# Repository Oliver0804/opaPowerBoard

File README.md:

# opaPowerBoard
## VER 1.0 202306

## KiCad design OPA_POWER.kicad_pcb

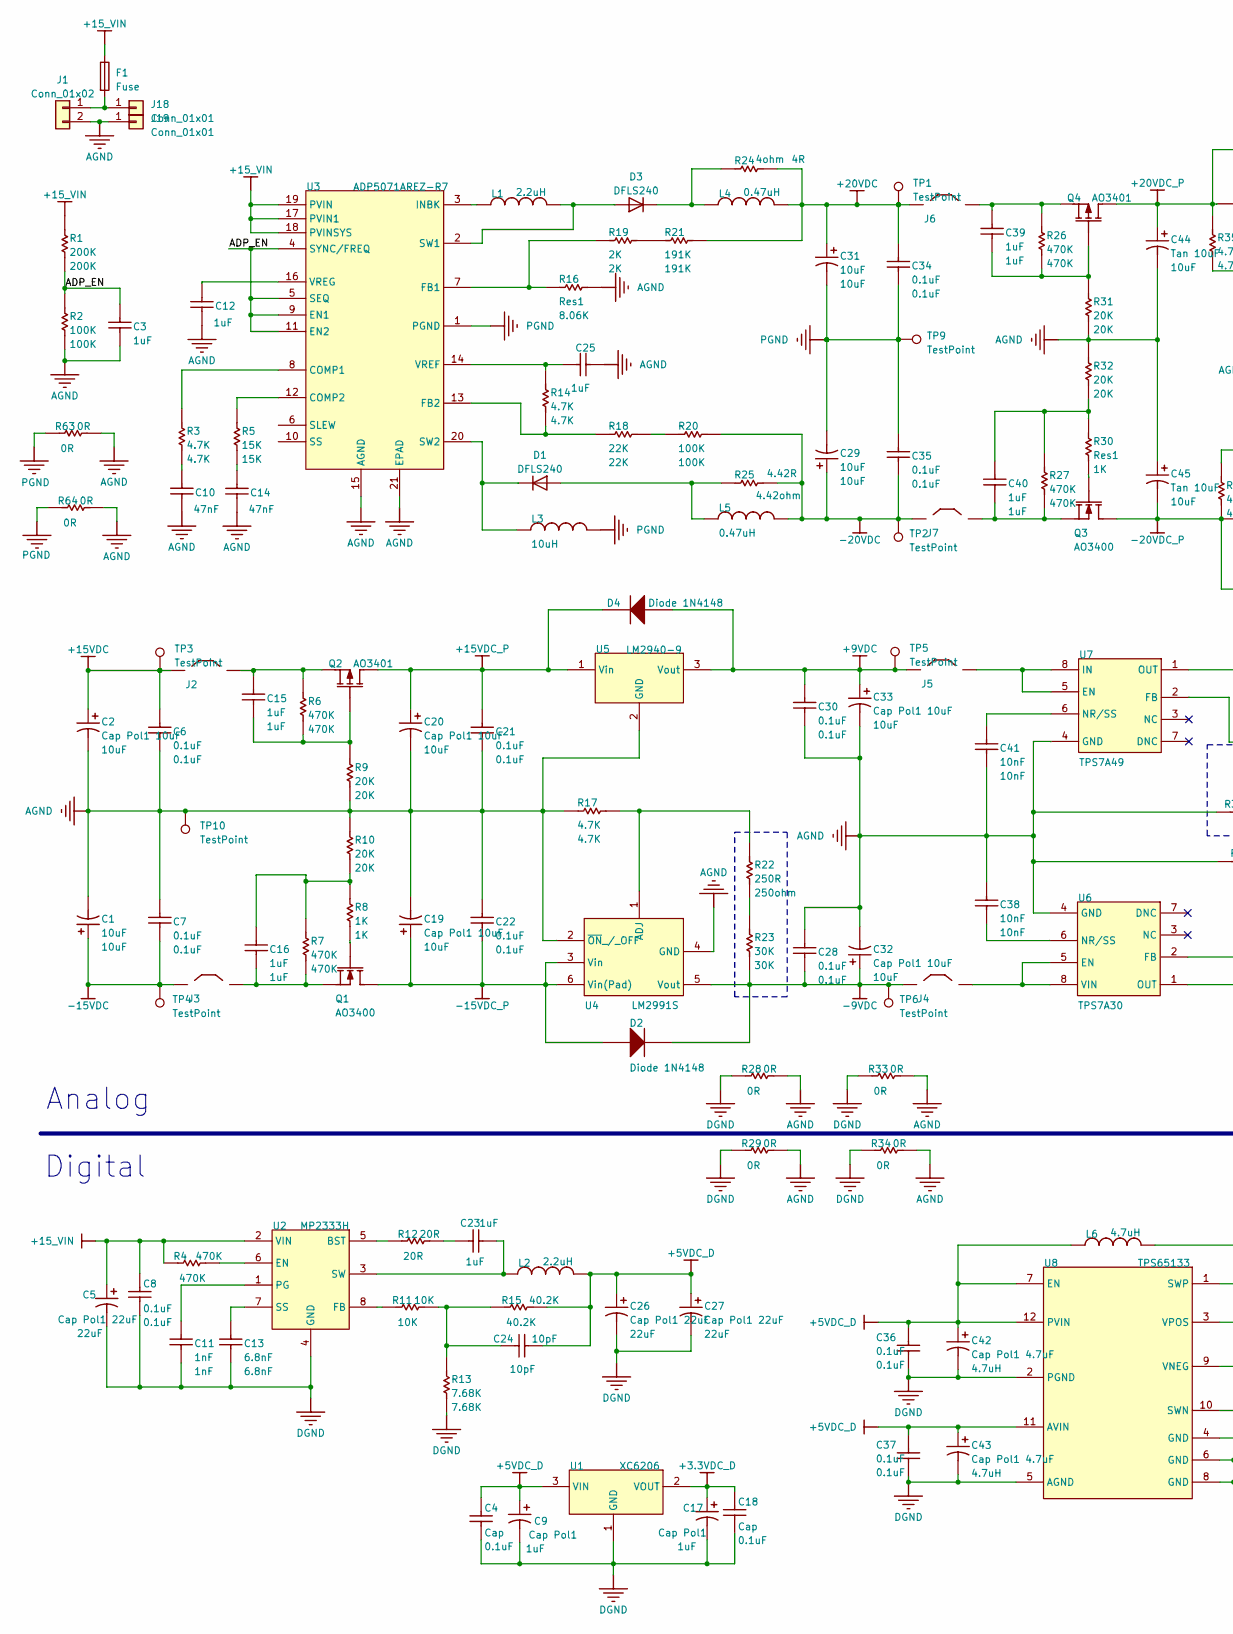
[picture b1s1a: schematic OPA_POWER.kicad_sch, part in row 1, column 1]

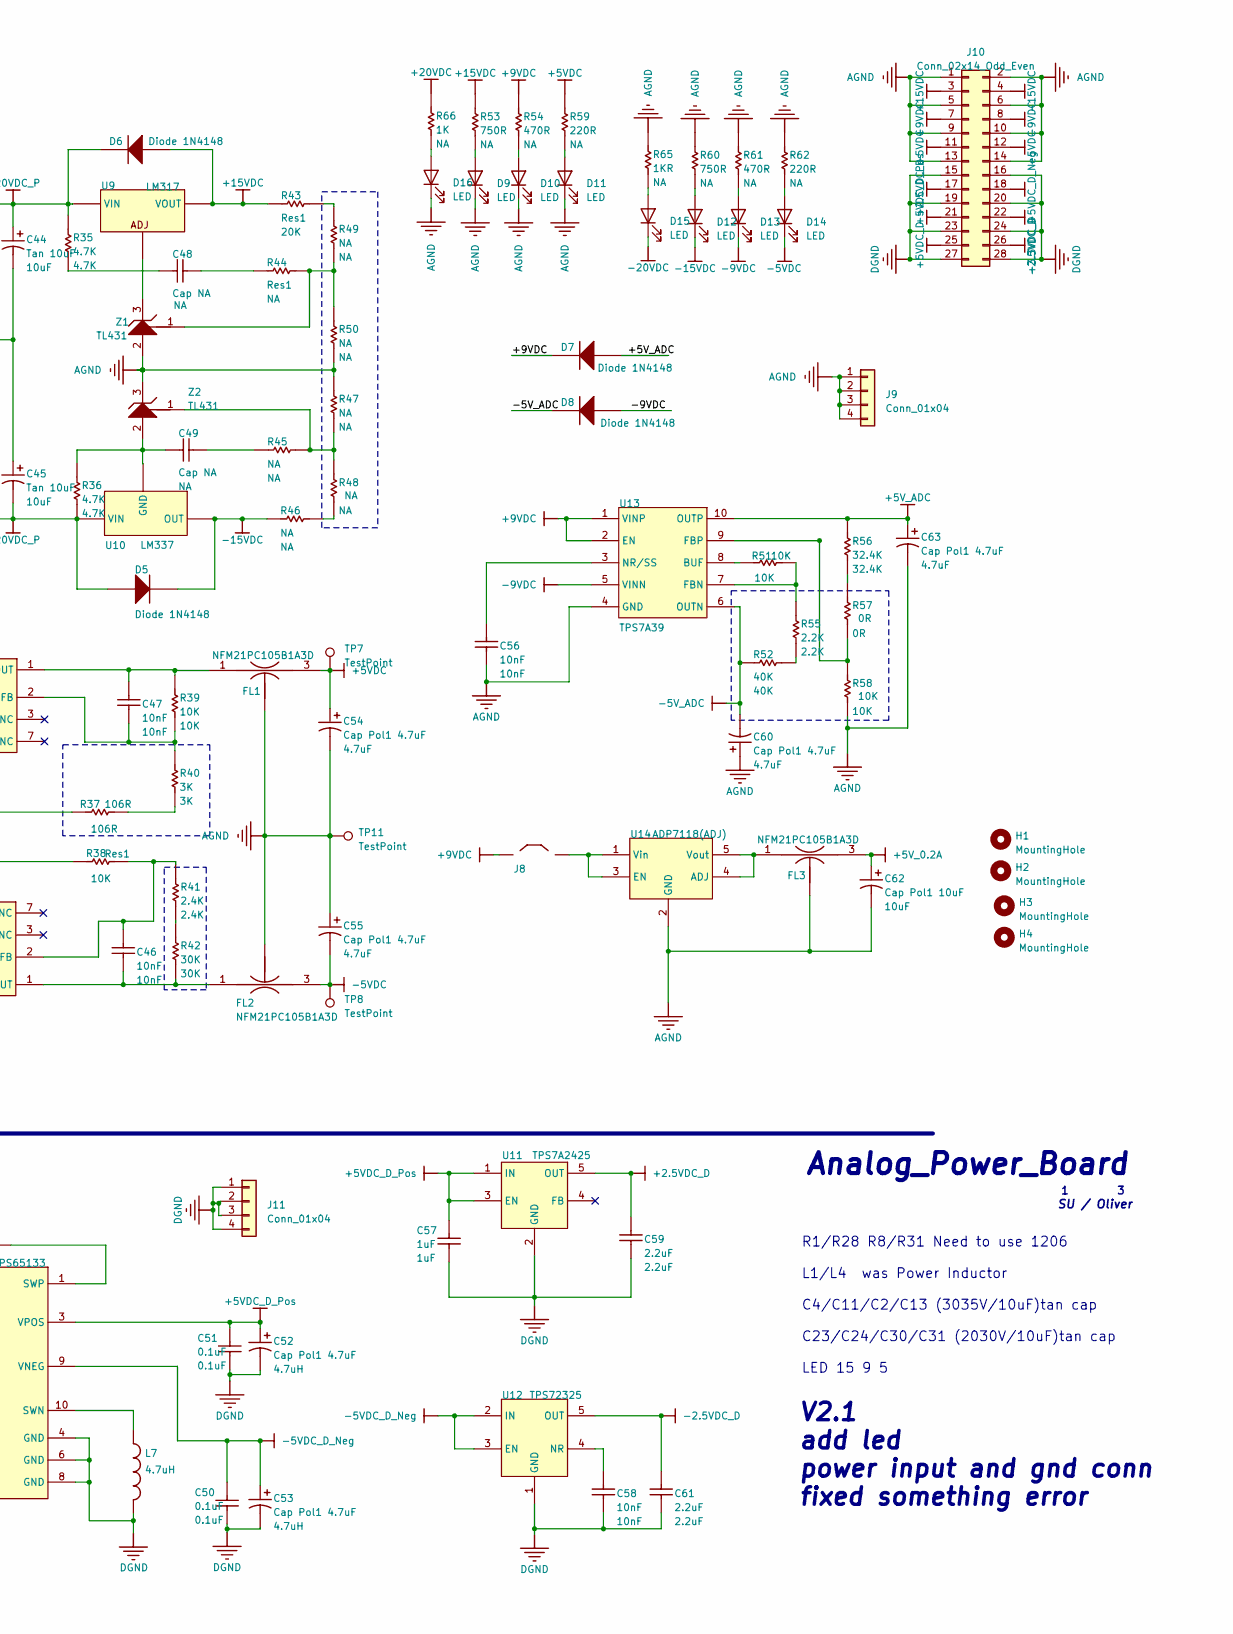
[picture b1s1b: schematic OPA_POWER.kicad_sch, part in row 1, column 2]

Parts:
C1, C29, C31: 10uF; CP_EIA-7343-20_Kemet-V
C2, C19, C20: Cap Pol1 10uF; CP_EIA-7343-20_Kemet-V
C3, C12, C15, C16, C23, C25, C39, C40, C57: 1uF; C_0603_1608Metric
C4, C18: Cap; C_0603_1608Metric
C5, C26, C27: Cap Pol1 22uF; CP_EIA-3528-12_Kemet-T
C6, C7, C8, C21, C22, C28, C30, C34, C35, C36, C37, C50, C51: 0.1uF; C_0603_1608Metric
C9, C17: Cap Pol1; CP_EIA-3528-12_Kemet-T
C10, C14: 47nF; C_0603_1608Metric
C11: 1nF; C_0603_1608Metric
C13: 6.8nF; C_0603_1608Metric
C24: 10pF; C_0603_1608Metric
C32, C33, C62: Cap Pol1 10uF; CP_EIA-3528-12_Kemet-T
C38, C41, C46, C47, C56, C58: 10nF; C_0603_1608Metric
C42, C52, C54: Cap Pol1 4.7uF; CP_EIA-3528-12_Kemet-T_Pad1.50x2.35mm_HandSolder
C43, C53, C55, C60, C63: Cap Pol1 4.7uF; CP_EIA-3528-12_Kemet-T
C44, C45: Tan 10uF; CP_EIA-7343-20_Kemet-V
C48, C49: Cap NA; C_0603_1608Metric
C59, C61: 2.2uF; C_0603_1608Metric
D1, D3: DFLS240; D_SOD-123
D2, D4, D5, D6, D7, D8: Diode 1N4148; D_SOD-323
D9, D10, D11, D12, D13, D14, D15, D16: LED; LED_0201_0603Metric
F1: Fuse; Fuse_1210_3225Metric
FL1, FL2, FL3: NFM21PC105B1A3D; FIL_NFM21PC105B1A3D
H1, H2, H3, H4: MountingHole; MountingHole_3mm_Pad_Via
J1: Conn_01x02; PinHeader_1x02_P2.54mm_Vertical
J2, J3, J4, J5, J6, J7, J8: Jumper; PinHeader_2x01_P2.54mm_Vertical
J9, J11: Conn_01x04; PinHeader_1x04_P2.54mm_Vertical
J10: Conn_02x14_Odd_Even; PinHeader_2x14_P2.54mm_Vertical
J18, J19: Conn_01x01; TestPoint_Pad_4.0x4.0mm
L1: 2.2uH; L_Vishay_IHLP-6767
L2: 2.2uH; L_Sunlord_SWPA3010S
L3: 10uH; L_Vishay_IHLP-6767
L4: 0.47uH; L_Sunlord_SWPA3010S
L5, L6: Inductor; L_Sunlord_SWPA3010S
L7: 4.7uH; L_Sunlord_SWPA3010S
Q1, Q3: AO3400; SOT-23
Q2, Q4: AO3401; SOT-23
R1: 200K; R_0603_1608Metric
R2, R20: 100K; R_0603_1608Metric
R3, R14, R17: 4.7K; R_0603_1608Metric
R4, R6, R7, R26, R27: 470K; R_0603_1608Metric
R5: 15K; R_0603_1608Metric
R8, R66: 1K; R_0603_1608Metric
R9, R10, R31, R32: 20K; R_0603_1608Metric
R11, R39, R51, R58: 10K; R_0603_1608Metric
R12: 20R; R_0603_1608Metric
R13: 7.68K; R_0603_1608Metric
R15: 40.2K; R_0603_1608Metric
R16, R30, R38, R43, R44: Res1; R_0603_1608Metric
R18: 22K; R_0603_1608Metric
R19: 2K; R_0603_1608Metric
R21: 191K; R_0603_1608Metric
R22: 250R; R_0603_1608Metric
R23, R42: 30K; R_0603_1608Metric
R24: 4R; R_1206_3216Metric
R25: 4.42R; R_1206_3216Metric
R28, R29, R33, R34, R57, R63, R64: 0R; R_0603_1608Metric
R35, R36: 4.7K; R_1206_3216Metric
R37: 106R; R_0603_1608Metric
R40: 3K; R_0603_1608Metric
R41: 2.4K; R_0603_1608Metric
R45, R46, R47, R48, R49, R50: NA; R_0603_1608Metric
R52: 40K; R_0603_1608Metric
R53, R60: 750R; R_0603_1608Metric
R54, R61: 470R; R_0603_1608Metric
R55: 2.2K; R_0603_1608Metric
R56: 32.4K; R_0603_1608Metric
R59, R62: 220R; R_0603_1608Metric
R65: 1KR; R_0603_1608Metric
TP1, TP2, TP3, TP4, TP5, TP6, TP7, TP8, TP9, TP10, TP11: TestPoint; TestPoint_Pad_D2.5mm
U1: XC6206; SOT-23
U2: MP2333H; SOT-583-8
U3: ADP5071AREZ-R7; HTSSOP-20-1EP_4.4x6.5mm_P0.65mm_EP3.4x6.5mm_Mask2.75x3.43mm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
U4: LM2991S; TO-263-5_TabPin3
U5: LM2940-9; TO-263-3_TabPin2
U6: TPS7A30; TSSOP-8_3x3mm_P0.65mm
U7: TPS7A49; TSSOP-8_3x3mm_P0.65mm
U8: TPS65133; WSON-12-1EP_4x4mm_P0.5mm_EP2.6x3mm_ThermalVias
U9: LM317; TO-263-3_TabPin2
U10: LM337; TO-263-3_TabPin2
U11: TPS7A2425; SOT-23-5
U12: TPS72325; SOT-23-5
U13: TPS7A39; TSSOP-8_3x3mm_P0.65mm
U14: ADP7118(ADJ); SOT-23-5
Z1, Z2: TL431; SOT-23

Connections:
+2.5VDC_D: C59.2, J10.21, U11.5 (OUT)
+3.3VDC_D: C17.1, C18.1, J10.26, U1.2 (VOUT)
+5VDC: C54.1, FL1.3 (OUT), J10.11, R59.1, TP7.1
+5VDC_D: C4.1, C9.1, C24.1, C26.1, C27.1, C36.1, C37.1, C42.1, C43.1, J10.25, L2.2, L6.1, R15.1, U1.3 (VIN), U8.7 (EN), U8.11 (AVIN), U8.12 (PVIN)
+5VDC_D_Pos: C51.1, C52.1, C57.1, J10.17, U8.3 (VPOS), U11.1 (IN), U11.3 (EN)
+5V_0.2A: C62.1, FL3.3 (OUT)
+5V_ADC: C63.1, D7.1 (A), R56.2, U13.10 (OUTP)
+9VDC: C30.1, C33.1, D4.1 (A), D7.2 (K), J5.1 (C1), J8.1 (C1), J10.7, R54.1, TP5.1, U5.3 (Vout), U13.1 (VINP), U13.2 (EN)
+15VDC: C2.1, C6.2, D6.1 (A), J2.1 (C1), J10.3, R43.1, R53.1, TP3.1, U9.2 (VOUT)
+15VDC_P: C20.1, C21.2, D4.2 (K), Q2.3 (D), U5.1 (Vin)
+15_VIN: C5.1, C8.1, F1.1, R1.2, R4.2, U2.2 (VIN), U3.17 (PVIN1), U3.18 (PVINSYS), U3.19 (PVIN)
+20VDC: C31.1, C34.2, J6.1 (C1), L4.2, R21.1, R24.1, R66.1, TP1.1
+20VDC_P: C44.1, D6.2 (K), Q4.3 (D), R35.2, U9.3 (VIN)
-2.5VDC_D: C61.2, J10.22, U12.5 (OUT)
-5VDC: C55.2, D14.1 (K), FL2.3 (OUT), J10.12, TP8.1
-5VDC_D_Neg: C50.1, C53.1, J10.18, U8.9 (VNEG), U12.2 (IN), U12.3 (EN)
-5V_ADC: C60.2, D8.2 (K), R52.1, U13.6 (OUTN)
-9VDC: C28.1, C32.1, D2.2 (K), D8.1 (A), D13.1 (K), J4.1 (C1), J10.8, R23.1, TP6.1, U4.5 (Vout), U13.5 (VINN)
-15VDC: C1.1, C7.1, D5.2 (K), D12.1 (K), J3.1 (C1), J10.4, R46.2, TP4.1, U10.3 (OUT)
-15VDC_P: C19.1, C22.1, D2.1 (A), Q1.3 (D), U4.3 (Vin), U4.6 (Vin(Pad))
-20VDC: C29.1, C35.1, D15.1 (K), J7.1 (C1), L5.2, R20.2, R25.1, TP2.1
-20VDC_P: C45.2, D5.1 (A), Q3.3 (D), R36.2, U10.2 (VIN)
/ADP_EN: C3.2, R1.1, R2.1, U3.4 (SYNC/FREQ), U3.5 (SEQ), U3.9 (EN1), U3.11 (EN2)
AGND: C1.2, C2.2, C3.1, C6.1, C7.2, C10.1, C12.1, C14.1, C19.2, C20.2, C21.1, C22.2, C25.2, C28.2, C30.2, C32.2, C33.2, C38.2, C41.2, C44.2, C45.1, C54.2, C55.1, C56.1, C60.1, C62.2, C63.2, D9.1 (K), D10.1 (K), D11.1 (K), D16.1 (K), FL1.2 (GND), FL1.2_1 (GND), FL1.2_3 (GND), FL2.2 (GND), FL2.2_1 (GND), FL2.2_3 (GND), FL3.2 (GND), FL3.2_1 (GND), FL3.2_3 (GND), J1.2, J9.1, J9.2, J9.3, J9.4, J10.1, J10.2, J10.5, J10.6, J10.9, J10.10, J10.13, J10.14, J19.1, R2.2, R9.2, R10.1, R16.1, R17.2, R28.1, R29.1, R31.2, R32.1, R33.1, R34.1, R37.2, R38.2, R47.2, R50.2, R58.1, R60.1, R61.1, R62.1, R63.1, R64.1, R65.1, TP10.1, TP11.1, U3.15 (AGND), U3.21 (EPAD), U4.2 (~ON_/_OFF), U4.4 (GND), U5.2 (GND), U6.4 (GND), U7.4 (GND), U13.4 (GND), U14.2 (GND), Z1.2 (ANODE), Z2.3 (CATHODE)
DGND: C4.2, C5.2, C8.2, C9.2, C11.1, C13.1, C17.2, C18.2, C26.2, C27.2, C36.2, C37.2, C42.2, C43.2, C50.2, C51.2, C52.2, C53.2, C57.2, C58.1, C59.1, C61.1, J10.15, J10.16, J10.19, J10.20, J10.23, J10.24, J10.27, J10.28, J11.1, J11.2, J11.3, J11.4, L7.2, R13.1, R28.2, R29.2, R33.2, R34.2, U1.1 (GND), U2.4 (GND), U8.2 (PGND), U8.4 (GND), U8.5 (AGND), U8.6 (GND), U8.8 (GND), U11.2 (GND), U12.1 (GND)
unnamed: C10.2, R3.1
unnamed: C14.2, R5.1
unnamed: C16.2, R7.2, R8.2, R10.2
unnamed: C23.2, R12.1
unnamed: C24.2, R11.1, R13.2, R15.2
unnamed: C40.2, R27.2, R30.2, R32.2
unnamed: C48.1, R44.2
unnamed: C48.2, R35.1
unnamed: C49.1, R45.2
unnamed: D1.2 (A), L5.1, R25.2
unnamed: D1.1 (K), L3.1, U3.20 (SW2)
unnamed: D3.2 (A), L1.2, U3.2 (SW1)
unnamed: D3.1 (K), L4.1, R24.2
unnamed: D9.2 (A), R53.2
unnamed: D10.2 (A), R54.2
unnamed: D11.2 (A), R59.2
unnamed: D12.2 (A), R60.2
unnamed: D13.2 (A), R61.2
unnamed: D14.2 (A), R62.2
unnamed: D15.2 (A), R65.2
unnamed: D16.2 (A), R66.2
unnamed: C47.2, FL1.1 (IN), R39.2, U7.1 (OUT)
unnamed: C46.1, FL2.1 (IN), R42.2, U6.1 (OUT)
unnamed: FL3.1 (IN), U14.4 (ADJ), U14.5 (Vout)
unnamed: F1.2, J1.1, J18.1
unnamed: C15.2, J2.2 (C2), Q2.2 (S), R6.2
unnamed: C16.1, J3.2 (C2), Q1.2 (S), R7.1
unnamed: J4.2 (C2), U6.5 (EN), U6.8 (VIN)
unnamed: J5.2 (C2), U7.5 (EN), U7.8 (IN)
unnamed: C39.2, J6.2 (C2), Q4.2 (S), R26.2
unnamed: C40.1, J7.2 (C2), Q3.2 (S), R27.1
unnamed: J8.2 (C2), U14.1 (Vin), U14.3 (EN)
unnamed: Q1.1 (G), R8.1
unnamed: C15.1, Q2.1 (G), R6.1, R9.1
unnamed: Q3.1 (G), R30.1
unnamed: C39.1, Q4.1 (G), R26.1, R31.1
unnamed: R18.2, R20.1
unnamed: R19.1, R21.2
unnamed: R22.1, R23.2
unnamed: R37.1, R40.1
unnamed: R41.1, R42.1
unnamed: R43.2, R49.1
unnamed: R46.1, R48.1
unnamed: R52.2, R55.2
unnamed: R56.1, R57.2
unnamed: R12.2, U2.5 (BST)
unnamed: R4.1, U2.6 (EN)
unnamed: R11.2, U2.8 (FB)
unnamed: C11.2, U2.1 (PG)
unnamed: C13.2, U2.7 (SS)
unnamed: C23.1, L2.1, U2.3 (SW)
unnamed: R3.2, U3.8 (COMP1)
unnamed: R5.2, U3.12 (COMP2)
unnamed: R16.2, R19.2, U3.7 (FB1)
unnamed: R14.1, R18.1, U3.13 (FB2)
unnamed: L1.1, U3.3 (INBK)
unnamed: C25.1, R14.2, U3.14 (VREF)
unnamed: C12.2, U3.16 (VREG)
unnamed: R17.1, R22.2, U4.1 (ADJ)
unnamed: C46.2, R38.1, R41.2, U6.2 (FB)
unnamed: C38.1, U6.6 (NR/SS)
unnamed: C47.1, R39.1, R40.2, U7.2 (FB)
unnamed: C41.1, U7.6 (NR/SS)
unnamed: L7.1, U8.10 (SWN)
unnamed: L6.2, U8.1 (SWP)
unnamed: U9.1 (ADJ), Z1.3 (CATHODE)
unnamed: C49.2, R36.1, U10.1 (GND), Z2.2 (ANODE)
unnamed: C58.2, U12.4 (NR)
unnamed: R51.1, U13.8 (BUF)
unnamed: R51.2, R55.1, U13.7 (FBN)
unnamed: R57.1, R58.2, U13.9 (FBP)
unnamed: C56.2, U13.3 (NR/SS)
unnamed: R44.1, R49.2, R50.1, Z1.1 (REF)
unnamed: R45.1, R47.1, R48.2, Z2.1 (REF)
PGND: C29.2, C31.2, C34.1, C35.2, L3.2, R63.2, R64.2, TP9.1, U3.1 (PGND)

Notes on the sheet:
SU / Oliver
V2.1 add led power input and gnd conn fixed something error
Digital
Analog_Power_Board
R1/R28 R8/R31 Need to use 1206 L1/L4 was Power Inductor C4/C11/C2/C13 (3035V/10uF)tan cap C23/C24/C30/C31 (2030V/10uF)tan cap LED 15 9 5
Analog

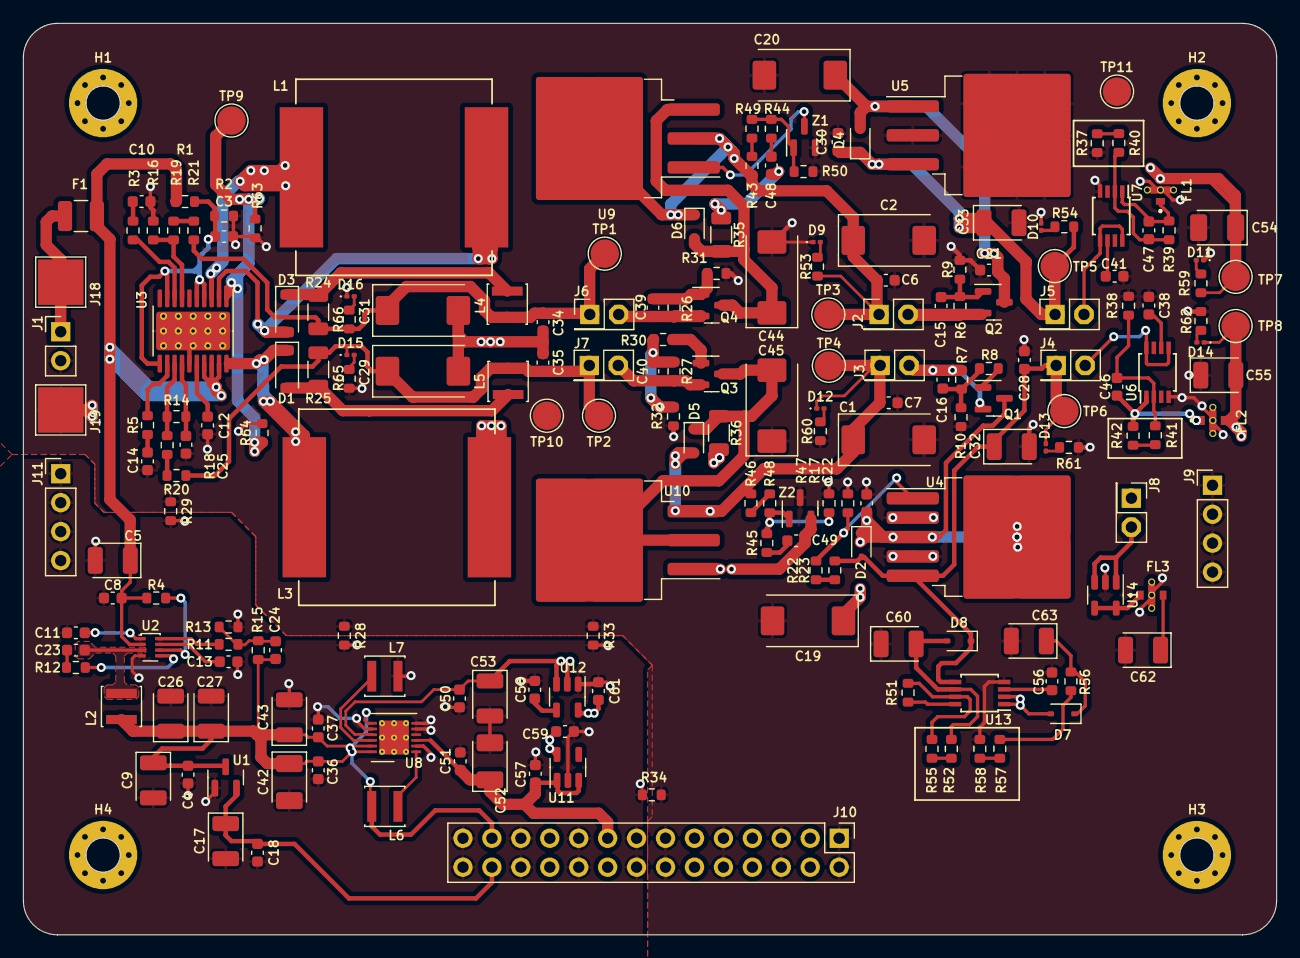
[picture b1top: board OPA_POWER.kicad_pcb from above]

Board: 4 copper layers, 110.0 x 80.0 mm, 204 parts (0 on the bottom side), 100 nets.

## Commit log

2023-06-08 第一次版本發布製作
2023-06-08 更新預覽圖
2023-06-08 添加readme
2023-06-09 更新庫＂
